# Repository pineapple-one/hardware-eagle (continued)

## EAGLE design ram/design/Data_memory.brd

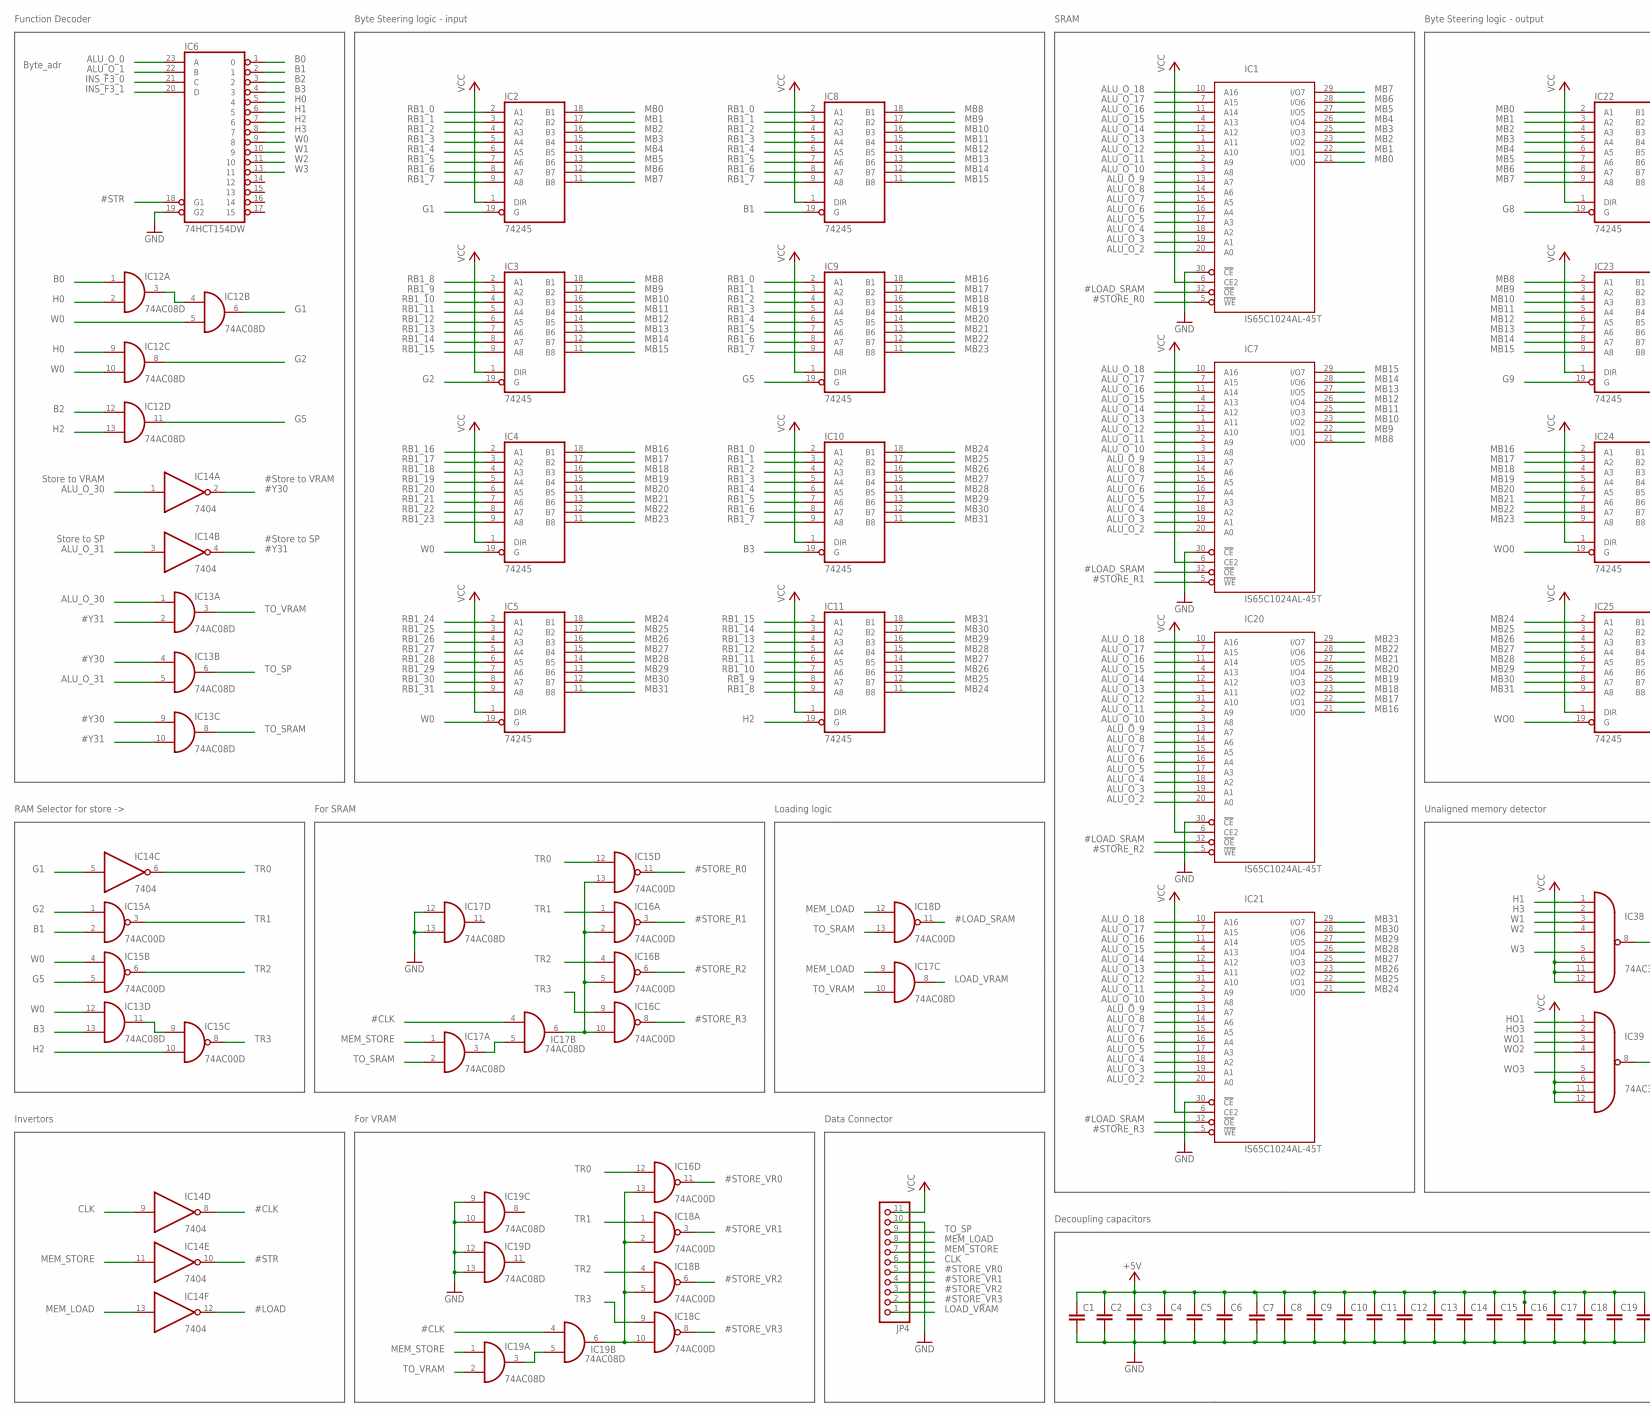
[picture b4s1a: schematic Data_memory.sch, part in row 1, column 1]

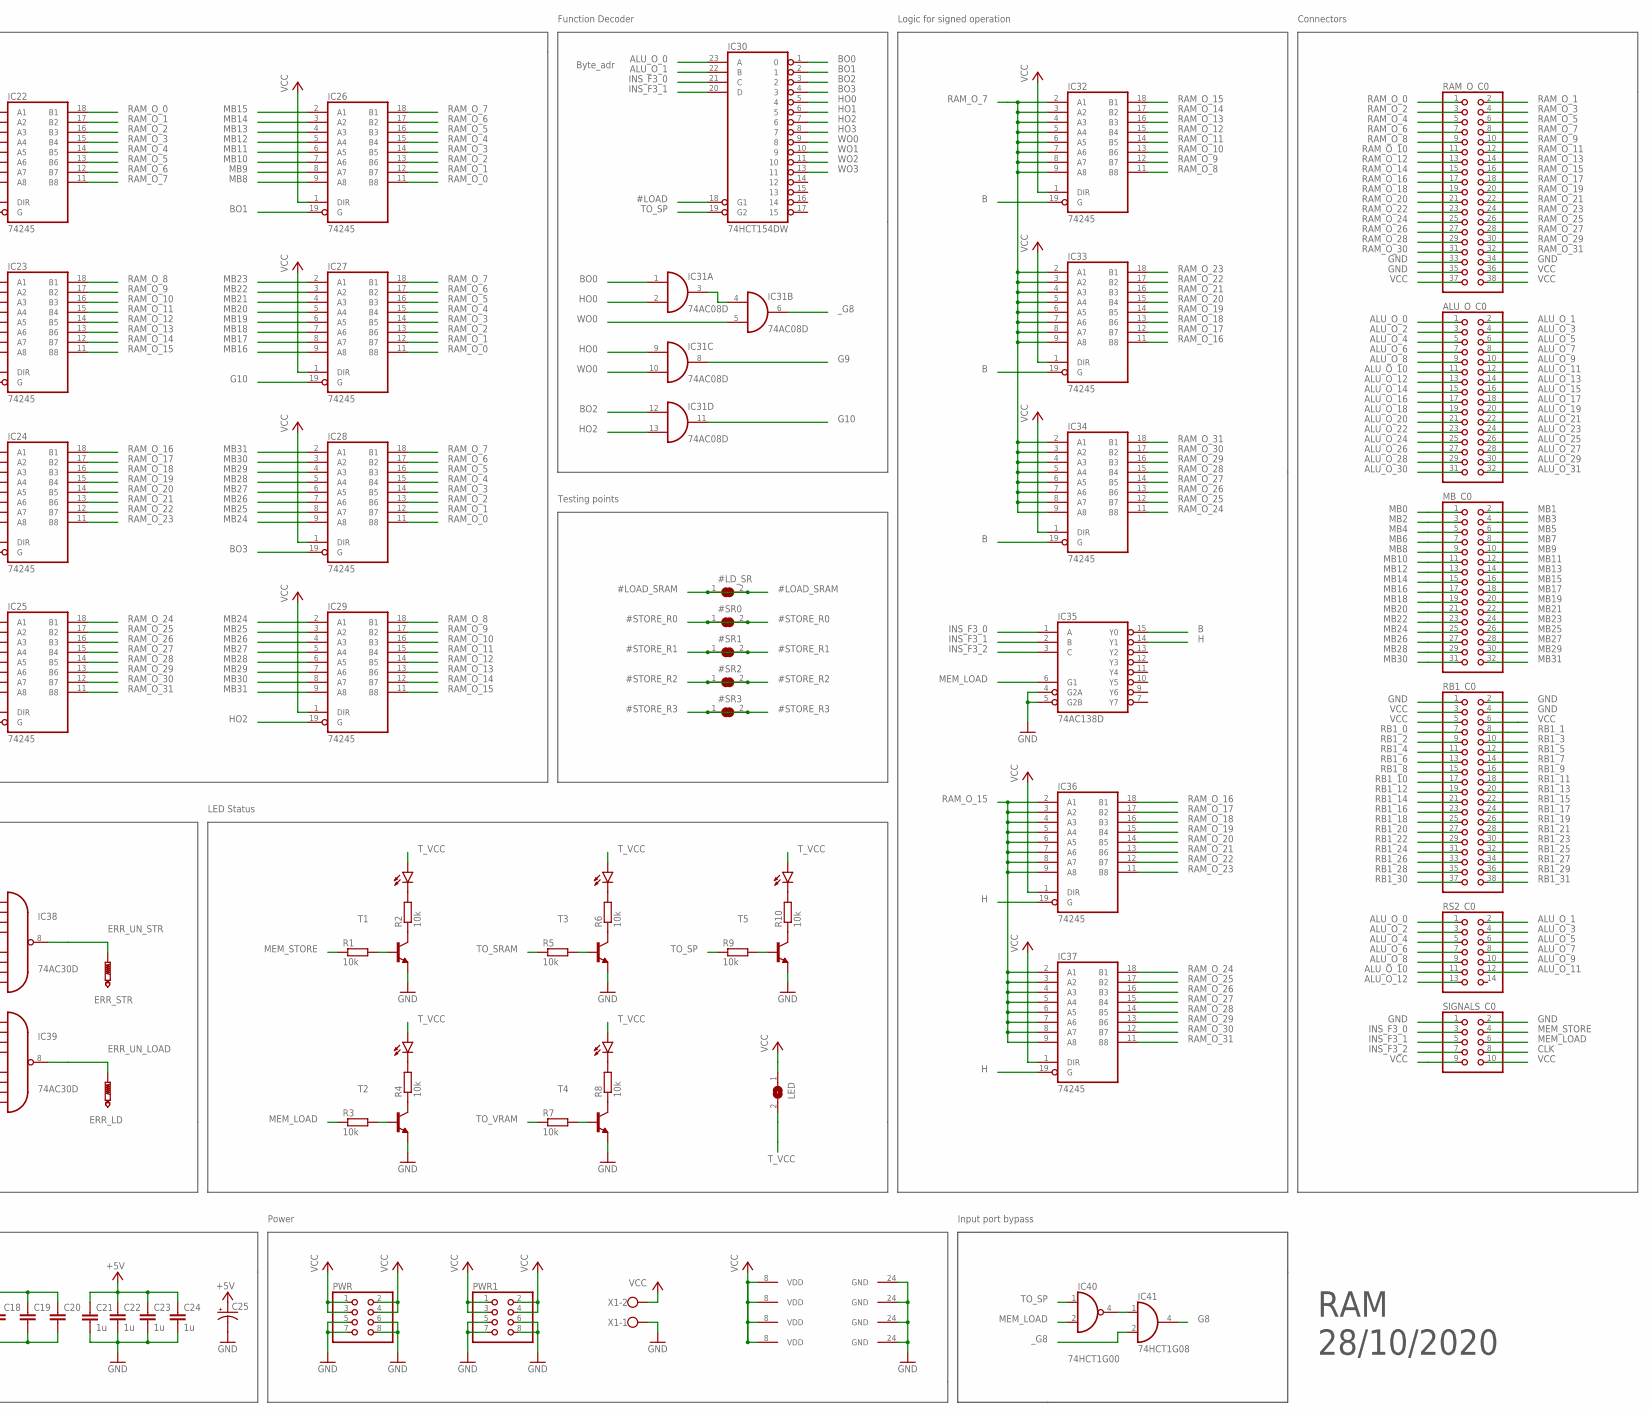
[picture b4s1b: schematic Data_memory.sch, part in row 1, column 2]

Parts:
#LD_SR: SJ
#SR0, #SR1, #SR2, #SR3: SJ
ALU_O_C0: PINHD-2X16; 2X16
C1, C2, C3, C4, C5, C6, C7, C8, C9, C10, C11, C12, C13, C14, C15, C16, C17, C18, C19, C20: C-EUC0805; C0805
C21, C22, C23, C24: 1u; C0805
C25: CAPACITOR-P153CLV-1010; 153CLV-1010
ERR_LD: PTR1B2,54; B2,54
ERR_STR: PTR1B2,54; B2,54
IC1, IC7, IC20, IC21: IS65C1024AL-45T; TSOP-I-32-8X20MM
IC2, IC3, IC4, IC5, IC8, IC9, IC10, IC11, IC22, IC23, IC24, IC25, IC26, IC27, IC28, IC29, IC32, IC33, IC34, IC36, IC37: 74245; TSSOP20
IC6, IC30: 74HCT154DW; SO24W
IC12, IC13, IC17, IC19, IC31: 74AC08D; SO14
IC14: 7404; TSSOP14
IC15, IC16, IC18: 74AC00D; SO14
IC35: 74AC138D; SO16
IC38, IC39: 74AC30D; SO14
IC40: 74HCT1G00; SOT23-5
IC41: 74HCT1G08; SOT23-5
JP4: PINHD-1X11; 1X11
LED: SJ
LED1, LED2, LED3, LED4, LED8: LEDSML0805; SML0805
MB_C0: PINHD-2X16; 2X16
PWR, PWR1: PINHD-2X4; 2X04
R1, R2, R3, R4, R5, R6, R7, R8, R9, R10: 10k; M0805
RAM_O_C0: PINHD-2X19; 2X19
RB1_C0: PINHD-2X19; 2X19
RS2_C0: PINHD-2X7; 2X07
SIGNALS_C0: PINHD-2X5; 2X05
T1, T2, T3, T4, T5: MMBT4401LT1-NPN-SOT23-BEC; SOT23-BEC
X1: W237-102

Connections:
#CLK: IC14.8 (O), IC17.4 (I0), IC19.4 (I0)
#LOAD: IC14.12 (O), IC30.18 (G1)
#LOAD_SRAM: #LD_SR.1, #LD_SR.2, IC1.32 (!OE), IC7.32 (!OE), IC18.11 (O), IC20.32 (!OE), IC21.32 (!OE)
#STORE_R0: #SR0.1, #SR0.2, IC1.5 (!WE), IC15.11 (O)
#STORE_R1: #SR1.1, #SR1.2, IC7.5 (!WE), IC16.3 (O)
#STORE_R2: #SR2.1, #SR2.2, IC16.6 (O), IC20.5 (!WE)
#STORE_R3: #SR3.1, #SR3.2, IC16.8 (O), IC21.5 (!WE)
#STORE_VR0: IC16.11 (O), JP4.5
#STORE_VR1: IC18.3 (O), JP4.4
#STORE_VR2: IC18.6 (O), JP4.3
#STORE_VR3: IC18.8 (O), JP4.2
#STR: IC6.18 (G1), IC14.10 (O)
#Y30: IC13.4 (I0), IC13.9 (I0), IC14.2 (O)
#Y31: IC13.2 (I1), IC13.10 (I1), IC14.4 (O)
ALU_O_0: ALU_O_C0.1, IC6.23 (A), IC30.23 (A), RS2_C0.1
ALU_O_1: ALU_O_C0.2, IC6.22 (B), IC30.22 (B), RS2_C0.2
ALU_O_2: ALU_O_C0.3, IC1.20 (A0), IC7.20 (A0), IC20.20 (A0), IC21.20 (A0), RS2_C0.3
ALU_O_3: ALU_O_C0.4, IC1.19 (A1), IC7.19 (A1), IC20.19 (A1), IC21.19 (A1), RS2_C0.4
ALU_O_4: ALU_O_C0.5, IC1.18 (A2), IC7.18 (A2), IC20.18 (A2), IC21.18 (A2), RS2_C0.5
ALU_O_5: ALU_O_C0.6, IC1.17 (A3), IC7.17 (A3), IC20.17 (A3), IC21.17 (A3), RS2_C0.6
ALU_O_6: ALU_O_C0.7, IC1.16 (A4), IC7.16 (A4), IC20.16 (A4), IC21.16 (A4), RS2_C0.7
ALU_O_7: ALU_O_C0.8, IC1.15 (A5), IC7.15 (A5), IC20.15 (A5), IC21.15 (A5), RS2_C0.8
ALU_O_8: ALU_O_C0.9, IC1.14 (A6), IC7.14 (A6), IC20.14 (A6), IC21.14 (A6), RS2_C0.9
ALU_O_9: ALU_O_C0.10, IC1.13 (A7), IC7.13 (A7), IC20.13 (A7), IC21.13 (A7), RS2_C0.10
ALU_O_10: ALU_O_C0.11, IC1.3 (A8), IC7.3 (A8), IC20.3 (A8), IC21.3 (A8), RS2_C0.11
ALU_O_11: ALU_O_C0.12, IC1.2 (A9), IC7.2 (A9), IC20.2 (A9), IC21.2 (A9), RS2_C0.12
ALU_O_12: ALU_O_C0.13, IC1.31 (A10), IC7.31 (A10), IC20.31 (A10), IC21.31 (A10), RS2_C0.13
ALU_O_13: ALU_O_C0.14, IC1.1 (A11), IC7.1 (A11), IC20.1 (A11), IC21.1 (A11)
ALU_O_14: ALU_O_C0.15, IC1.12 (A12), IC7.12 (A12), IC20.12 (A12), IC21.12 (A12)
ALU_O_15: ALU_O_C0.16, IC1.4 (A13), IC7.4 (A13), IC20.4 (A13), IC21.4 (A13)
ALU_O_16: ALU_O_C0.17, IC1.11 (A14), IC7.11 (A14), IC20.11 (A14), IC21.11 (A14)
ALU_O_17: ALU_O_C0.18, IC1.7 (A15), IC7.7 (A15), IC20.7 (A15), IC21.7 (A15)
ALU_O_18: ALU_O_C0.19, IC1.10 (A16), IC7.10 (A16), IC20.10 (A16), IC21.10 (A16)
ALU_O_19: ALU_O_C0.20
ALU_O_20: ALU_O_C0.21
ALU_O_21: ALU_O_C0.22
ALU_O_22: ALU_O_C0.23
ALU_O_23: ALU_O_C0.24
ALU_O_24: ALU_O_C0.25
ALU_O_25: ALU_O_C0.26
ALU_O_26: ALU_O_C0.27
ALU_O_27: ALU_O_C0.28
ALU_O_28: ALU_O_C0.29
ALU_O_29: ALU_O_C0.30
ALU_O_30: ALU_O_C0.31, IC13.1 (I0), IC14.1 (I)
ALU_O_31: ALU_O_C0.32, IC13.5 (I1), IC14.3 (I)
B: IC32.19 (G), IC33.19 (G), IC34.19 (G), IC35.15 (Y0)
B0: IC6.1 (0), IC12.1 (I0)
B1: IC6.2 (1), IC8.19 (G), IC15.2 (I1)
B2: IC6.3 (2), IC12.12 (I0)
B3: IC6.4 (3), IC10.19 (G), IC13.13 (I1)
BO0: IC30.1 (0), IC31.1 (I0)
BO1: IC26.19 (G), IC30.2 (1)
BO2: IC30.3 (2), IC31.12 (I0)
BO3: IC28.19 (G), IC30.4 (3)
CLK: IC14.9 (I), JP4.6, SIGNALS_C0.8
ERR_UN_LOAD: ERR_LD.TP, IC39.8 (O)
ERR_UN_STR: ERR_STR.TP, IC38.8 (O)
G1: IC2.19 (G), IC12.6 (O), IC14.5 (I)
G2: IC3.19 (G), IC12.8 (O), IC15.1 (I0)
G5: IC9.19 (G), IC12.11 (O), IC15.5 (I1)
G8: IC22.19 (G), IC41.4 (O)
G9: IC23.19 (G), IC31.8 (O)
G10: IC27.19 (G), IC31.11 (O)
GND: C1.2, C2.2, C3.2, C4.2, C5.2, C6.2, C7.2, C8.2, C9.2, C10.2, C11.2, C12.2, C13.2, C14.2, C15.2, C16.2, C17.2, C18.2, C19.2, C20.2, C21.2, C22.2, C23.2, C24.2, C25.-, IC1.24 (GND), IC1.30 (!CE), IC2.10 (GND), IC3.10 (GND), IC4.10 (GND), IC5.10 (GND), IC6.12 (GND), IC6.19 (G2), IC7.24 (GND), IC7.30 (!CE), IC8.10 (GND), IC9.10 (GND), IC10.10 (GND), IC11.10 (GND), IC12.7 (GND), IC13.7 (GND), IC14.7 (GND), IC15.7 (GND), IC16.7 (GND), IC17.7 (GND), IC17.12 (I0), IC17.13 (I1), IC18.7 (GND), IC19.7 (GND), IC19.9 (I0), IC19.10 (I1), IC19.12 (I0), IC19.13 (I1), IC20.24 (GND), IC20.30 (!CE), IC21.24 (GND), IC21.30 (!CE), IC22.10 (GND), IC23.10 (GND), IC24.10 (GND), IC25.10 (GND), IC26.10 (GND), IC27.10 (GND), IC28.10 (GND), IC29.10 (GND), IC30.12 (GND), IC31.7 (GND), IC32.10 (GND), IC33.10 (GND), IC34.10 (GND), IC35.4 (G2A), IC35.5 (G2B), IC35.8 (GND), IC36.10 (GND), IC37.10 (GND), IC38.7 (GND), IC39.7 (GND), IC40.3 (GND), IC41.3 (GND), JP4.10, PWR.5, PWR.6, PWR.7, PWR.8, PWR1.5, PWR1.6, PWR1.7, PWR1.8, RAM_O_C0.33, RAM_O_C0.34, RAM_O_C0.35, RB1_C0.1, RB1_C0.2, RB1_C0.4, SIGNALS_C0.1, SIGNALS_C0.2, T1.E, T2.E, T3.E, T4.E, T5.E, X1.1
H: IC35.14 (Y1), IC36.19 (G), IC37.19 (G)
H0: IC6.5 (4), IC12.2 (I1), IC12.9 (I0)
H1: IC6.6 (5), IC38.1 (I0)
H2: IC6.7 (6), IC11.19 (G), IC12.13 (I1), IC15.10 (I1)
H3: IC6.8 (7), IC38.2 (I1)
HO0: IC30.5 (4), IC31.2 (I1), IC31.9 (I0)
HO1: IC30.6 (5), IC39.1 (I0)
HO2: IC29.19 (G), IC30.7 (6), IC31.13 (I1)
HO3: IC30.8 (7), IC39.2 (I1)
INS_F3_0: IC6.21 (C), IC30.21 (C), IC35.1 (A), SIGNALS_C0.3
INS_F3_1: IC6.20 (D), IC30.20 (D), IC35.2 (B), SIGNALS_C0.5
INS_F3_2: IC35.3 (C), SIGNALS_C0.7
LOAD_VRAM: IC17.8 (O), JP4.1
MB0: IC1.21 (I/O0), IC2.18 (B1), IC22.2 (A1), MB_C0.1
MB1: IC1.22 (I/O1), IC2.17 (B2), IC22.3 (A2), MB_C0.2
MB2: IC1.23 (I/O2), IC2.16 (B3), IC22.4 (A3), MB_C0.3
MB3: IC1.25 (I/O3), IC2.15 (B4), IC22.5 (A4), MB_C0.4
MB4: IC1.26 (I/O4), IC2.14 (B5), IC22.6 (A5), MB_C0.5
MB5: IC1.27 (I/O5), IC2.13 (B6), IC22.7 (A6), MB_C0.6
MB6: IC1.28 (I/O6), IC2.12 (B7), IC22.8 (A7), MB_C0.7
MB7: IC1.29 (I/O7), IC2.11 (B8), IC22.9 (A8), MB_C0.8
MB8: IC3.18 (B1), IC7.21 (I/O0), IC8.18 (B1), IC23.2 (A1), IC26.9 (A8), MB_C0.9
MB9: IC3.17 (B2), IC7.22 (I/O1), IC8.17 (B2), IC23.3 (A2), IC26.8 (A7), MB_C0.10
MB10: IC3.16 (B3), IC7.23 (I/O2), IC8.16 (B3), IC23.4 (A3), IC26.7 (A6), MB_C0.11
MB11: IC3.15 (B4), IC7.25 (I/O3), IC8.15 (B4), IC23.5 (A4), IC26.6 (A5), MB_C0.12
MB12: IC3.14 (B5), IC7.26 (I/O4), IC8.14 (B5), IC23.6 (A5), IC26.5 (A4), MB_C0.13
MB13: IC3.13 (B6), IC7.27 (I/O5), IC8.13 (B6), IC23.7 (A6), IC26.4 (A3), MB_C0.14
MB14: IC3.12 (B7), IC7.28 (I/O6), IC8.12 (B7), IC23.8 (A7), IC26.3 (A2), MB_C0.15
MB15: IC3.11 (B8), IC7.29 (I/O7), IC8.11 (B8), IC23.9 (A8), IC26.2 (A1), MB_C0.16
MB16: IC4.18 (B1), IC9.18 (B1), IC20.21 (I/O0), IC24.2 (A1), IC27.9 (A8), MB_C0.17
MB17: IC4.17 (B2), IC9.17 (B2), IC20.22 (I/O1), IC24.3 (A2), IC27.8 (A7), MB_C0.18
MB18: IC4.16 (B3), IC9.16 (B3), IC20.23 (I/O2), IC24.4 (A3), IC27.7 (A6), MB_C0.19
MB19: IC4.15 (B4), IC9.15 (B4), IC20.25 (I/O3), IC24.5 (A4), IC27.6 (A5), MB_C0.20
MB20: IC4.14 (B5), IC9.14 (B5), IC20.26 (I/O4), IC24.6 (A5), IC27.5 (A4), MB_C0.21
MB21: IC4.13 (B6), IC9.13 (B6), IC20.27 (I/O5), IC24.7 (A6), IC27.4 (A3), MB_C0.22
MB22: IC4.12 (B7), IC9.12 (B7), IC20.28 (I/O6), IC24.8 (A7), IC27.3 (A2), MB_C0.23
MB23: IC4.11 (B8), IC9.11 (B8), IC20.29 (I/O7), IC24.9 (A8), IC27.2 (A1), MB_C0.24
MB24: IC5.18 (B1), IC10.18 (B1), IC11.11 (B8), IC21.21 (I/O0), IC25.2 (A1), IC28.9 (A8), IC29.2 (A1), MB_C0.25
MB25: IC5.17 (B2), IC10.17 (B2), IC11.12 (B7), IC21.22 (I/O1), IC25.3 (A2), IC28.8 (A7), IC29.3 (A2), MB_C0.26
MB26: IC5.16 (B3), IC10.16 (B3), IC11.13 (B6), IC21.23 (I/O2), IC25.4 (A3), IC28.7 (A6), IC29.4 (A3), MB_C0.27
MB27: IC5.15 (B4), IC10.15 (B4), IC11.14 (B5), IC21.25 (I/O3), IC25.5 (A4), IC28.6 (A5), IC29.5 (A4), MB_C0.28
MB28: IC5.14 (B5), IC10.14 (B5), IC11.15 (B4), IC21.26 (I/O4), IC25.6 (A5), IC28.5 (A4), IC29.6 (A5), MB_C0.29
MB29: IC5.13 (B6), IC10.13 (B6), IC11.16 (B3), IC21.27 (I/O5), IC25.7 (A6), IC28.4 (A3), IC29.7 (A6), MB_C0.30
MB30: IC5.12 (B7), IC10.12 (B7), IC11.17 (B2), IC21.28 (I/O6), IC25.8 (A7), IC28.3 (A2), IC29.8 (A7), MB_C0.31
MB31: IC5.11 (B8), IC10.11 (B8), IC11.18 (B1), IC21.29 (I/O7), IC25.9 (A8), IC28.2 (A1), IC29.9 (A8), MB_C0.32
MEM_LOAD: IC14.13 (I), IC17.9 (I0), IC18.12 (I0), IC35.6 (G1), IC40.2 (I1), JP4.8, R3.1, SIGNALS_C0.6
MEM_STORE: IC14.11 (I), IC17.1 (I0), IC19.1 (I0), JP4.7, R1.1, SIGNALS_C0.4
unnamed: IC12.3 (O), IC12.4 (I0)
unnamed: IC13.11 (O), IC15.9 (I0)
unnamed: IC17.3 (O), IC17.5 (I1)
unnamed: IC16.13 (I1), IC18.2 (I1), IC18.5 (I1), IC18.10 (I1), IC19.6 (O)
unnamed: IC19.3 (O), IC19.5 (I1)
unnamed: IC31.3 (O), IC31.4 (I0)
unnamed: IC15.13 (I1), IC16.2 (I1), IC16.5 (I1), IC16.10 (I1), IC17.6 (O)
unnamed: R1.2, T1.B
unnamed: R3.2, T2.B
unnamed: LED1.C, R2.2
unnamed: R2.1, T1.C
unnamed: LED8.C, R4.2
unnamed: R4.1, T2.C
unnamed: R5.2, T3.B
unnamed: LED2.C, R6.2
unnamed: R6.1, T3.C
unnamed: R7.2, T4.B
unnamed: LED3.C, R8.2
unnamed: R8.1, T4.C
unnamed: R9.2, T5.B
unnamed: LED4.C, R10.2
unnamed: R10.1, T5.C
unnamed: IC40.4 (O), IC41.1 (I0)
RAM_O_0: IC22.18 (B1), IC26.11 (B8), IC27.11 (B8), IC28.11 (B8), RAM_O_C0.1
RAM_O_1: IC22.17 (B2), IC26.12 (B7), IC27.12 (B7), IC28.12 (B7), RAM_O_C0.2
RAM_O_2: IC22.16 (B3), IC26.13 (B6), IC27.13 (B6), IC28.13 (B6), RAM_O_C0.3
RAM_O_3: IC22.15 (B4), IC26.14 (B5), IC27.14 (B5), IC28.14 (B5), RAM_O_C0.4
RAM_O_4: IC22.14 (B5), IC26.15 (B4), IC27.15 (B4), IC28.15 (B4), RAM_O_C0.5
RAM_O_5: IC22.13 (B6), IC26.16 (B3), IC27.16 (B3), IC28.16 (B3), RAM_O_C0.6
RAM_O_6: IC22.12 (B7), IC26.17 (B2), IC27.17 (B2), IC28.17 (B2), RAM_O_C0.7
RAM_O_7: IC22.11 (B8), IC26.18 (B1), IC27.18 (B1), IC28.18 (B1), IC32.2 (A1), IC32.3 (A2), IC32.4 (A3), IC32.5 (A4), IC32.6 (A5), IC32.7 (A6), IC32.8 (A7), IC32.9 (A8), IC33.2 (A1), IC33.3 (A2), IC33.4 (A3), IC33.5 (A4), IC33.6 (A5), IC33.7 (A6), IC33.8 (A7), IC33.9 (A8), IC34.2 (A1), IC34.3 (A2), IC34.4 (A3), IC34.5 (A4), IC34.6 (A5), IC34.7 (A6), IC34.8 (A7), IC34.9 (A8), RAM_O_C0.8
RAM_O_8: IC23.18 (B1), IC29.18 (B1), IC32.11 (B8), RAM_O_C0.9
RAM_O_9: IC23.17 (B2), IC29.17 (B2), IC32.12 (B7), RAM_O_C0.10
RAM_O_10: IC23.16 (B3), IC29.16 (B3), IC32.13 (B6), RAM_O_C0.11
RAM_O_11: IC23.15 (B4), IC29.15 (B4), IC32.14 (B5), RAM_O_C0.12
RAM_O_12: IC23.14 (B5), IC29.14 (B5), IC32.15 (B4), RAM_O_C0.13
RAM_O_13: IC23.13 (B6), IC29.13 (B6), IC32.16 (B3), RAM_O_C0.14
RAM_O_14: IC23.12 (B7), IC29.12 (B7), IC32.17 (B2), RAM_O_C0.15
RAM_O_15: IC23.11 (B8), IC29.11 (B8), IC32.18 (B1), IC36.2 (A1), IC36.3 (A2), IC36.4 (A3), IC36.5 (A4), IC36.6 (A5), IC36.7 (A6), IC36.8 (A7), IC36.9 (A8), IC37.2 (A1), IC37.3 (A2), IC37.4 (A3), IC37.5 (A4), IC37.6 (A5), IC37.7 (A6), IC37.8 (A7), IC37.9 (A8), RAM_O_C0.16
RAM_O_16: IC24.18 (B1), IC33.11 (B8), IC36.18 (B1), RAM_O_C0.17
RAM_O_17: IC24.17 (B2), IC33.12 (B7), IC36.17 (B2), RAM_O_C0.18
RAM_O_18: IC24.16 (B3), IC33.13 (B6), IC36.16 (B3), RAM_O_C0.19
RAM_O_19: IC24.15 (B4), IC33.14 (B5), IC36.15 (B4), RAM_O_C0.20
RAM_O_20: IC24.14 (B5), IC33.15 (B4), IC36.14 (B5), RAM_O_C0.21
RAM_O_21: IC24.13 (B6), IC33.16 (B3), IC36.13 (B6), RAM_O_C0.22
RAM_O_22: IC24.12 (B7), IC33.17 (B2), IC36.12 (B7), RAM_O_C0.23
RAM_O_23: IC24.11 (B8), IC33.18 (B1), IC36.11 (B8), RAM_O_C0.24
RAM_O_24: IC25.18 (B1), IC34.11 (B8), IC37.18 (B1), RAM_O_C0.25
RAM_O_25: IC25.17 (B2), IC34.12 (B7), IC37.17 (B2), RAM_O_C0.26
RAM_O_26: IC25.16 (B3), IC34.13 (B6), IC37.16 (B3), RAM_O_C0.27
RAM_O_27: IC25.15 (B4), IC34.14 (B5), IC37.15 (B4), RAM_O_C0.28
RAM_O_28: IC25.14 (B5), IC34.15 (B4), IC37.14 (B5), RAM_O_C0.29
RAM_O_29: IC25.13 (B6), IC34.16 (B3), IC37.13 (B6), RAM_O_C0.30
RAM_O_30: IC25.12 (B7), IC34.17 (B2), IC37.12 (B7), RAM_O_C0.31
RAM_O_31: IC25.11 (B8), IC34.18 (B1), IC37.11 (B8), RAM_O_C0.32
RB1_0: IC2.2 (A1), IC8.2 (A1), IC9.2 (A1), IC10.2 (A1), RB1_C0.7
RB1_1: IC2.3 (A2), IC8.3 (A2), IC9.3 (A2), IC10.3 (A2), RB1_C0.8
RB1_2: IC2.4 (A3), IC8.4 (A3), IC9.4 (A3), IC10.4 (A3), RB1_C0.9
RB1_3: IC2.5 (A4), IC8.5 (A4), IC9.5 (A4), IC10.5 (A4), RB1_C0.10
RB1_4: IC2.6 (A5), IC8.6 (A5), IC9.6 (A5), IC10.6 (A5), RB1_C0.11
RB1_5: IC2.7 (A6), IC8.7 (A6), IC9.7 (A6), IC10.7 (A6), RB1_C0.12
RB1_6: IC2.8 (A7), IC8.8 (A7), IC9.8 (A7), IC10.8 (A7), RB1_C0.13
RB1_7: IC2.9 (A8), IC8.9 (A8), IC9.9 (A8), IC10.9 (A8), RB1_C0.14
RB1_8: IC3.2 (A1), IC11.9 (A8), RB1_C0.15
RB1_9: IC3.3 (A2), IC11.8 (A7), RB1_C0.16
RB1_10: IC3.4 (A3), IC11.7 (A6), RB1_C0.17
RB1_11: IC3.5 (A4), IC11.6 (A5), RB1_C0.18
RB1_12: IC3.6 (A5), IC11.5 (A4), RB1_C0.19
RB1_13: IC3.7 (A6), IC11.4 (A3), RB1_C0.20
RB1_14: IC3.8 (A7), IC11.3 (A2), RB1_C0.21
RB1_15: IC3.9 (A8), IC11.2 (A1), RB1_C0.22
RB1_16: IC4.2 (A1), RB1_C0.23
RB1_17: IC4.3 (A2), RB1_C0.24
RB1_18: IC4.4 (A3), RB1_C0.25
RB1_19: IC4.5 (A4), RB1_C0.26
RB1_20: IC4.6 (A5), RB1_C0.27
RB1_21: IC4.7 (A6), RB1_C0.28
RB1_22: IC4.8 (A7), RB1_C0.29
RB1_23: IC4.9 (A8), RB1_C0.30
RB1_24: IC5.2 (A1), RB1_C0.31
RB1_25: IC5.3 (A2), RB1_C0.32
RB1_26: IC5.4 (A3), RB1_C0.33
RB1_27: IC5.5 (A4), RB1_C0.34
RB1_28: IC5.6 (A5), RB1_C0.35
RB1_29: IC5.7 (A6), RB1_C0.36
RB1_30: IC5.8 (A7), RB1_C0.37
RB1_31: IC5.9 (A8), RB1_C0.38
TO_SP: IC13.6 (O), IC30.19 (G2), IC40.1 (I0), JP4.9, R9.1
TO_SRAM: IC13.8 (O), IC17.2 (I1), IC18.13 (I1), R5.1
TO_VRAM: IC13.3 (O), IC17.10 (I1), IC19.2 (I1), R7.1
TR0: IC14.6 (O), IC15.12 (I0), IC16.12 (I0)
TR1: IC15.3 (O), IC16.1 (I0), IC18.1 (I0)
TR2: IC15.6 (O), IC16.4 (I0), IC18.4 (I0)
TR3: IC15.8 (O), IC16.9 (I0), IC18.9 (I0)
T_VCC: LED.2, LED1.A, LED2.A, LED3.A, LED4.A, LED8.A
VCC: C1.1, C2.1, C3.1, C4.1, C5.1, C6.1, C7.1, C8.1, C9.1, C10.1, C11.1, C12.1, C13.1, C14.1, C15.1, C16.1, C17.1, C18.1, C19.1, C20.1, C21.1, C22.1, C23.1, C24.1, C25.+, IC1.6 (CE2), IC1.8 (VDD), IC2.1 (DIR), IC2.20 (VCC), IC3.1 (DIR), IC3.20 (VCC), IC4.1 (DIR), IC4.20 (VCC), IC5.1 (DIR), IC5.20 (VCC), IC6.24 (VCC), IC7.6 (CE2), IC7.8 (VDD), IC8.1 (DIR), IC8.20 (VCC), IC9.1 (DIR), IC9.20 (VCC), IC10.1 (DIR), IC10.20 (VCC), IC11.1 (DIR), IC11.20 (VCC), IC12.14 (VCC), IC13.14 (VCC), IC14.14 (VCC), IC15.14 (VCC), IC16.14 (VCC), IC17.14 (VCC), IC18.14 (VCC), IC19.14 (VCC), IC20.6 (CE2), IC20.8 (VDD), IC21.6 (CE2), IC21.8 (VDD), IC22.1 (DIR), IC22.20 (VCC), IC23.1 (DIR), IC23.20 (VCC), IC24.1 (DIR), IC24.20 (VCC), IC25.1 (DIR), IC25.20 (VCC), IC26.1 (DIR), IC26.20 (VCC), IC27.1 (DIR), IC27.20 (VCC), IC28.1 (DIR), IC28.20 (VCC), IC29.1 (DIR), IC29.20 (VCC), IC30.24 (VCC), IC31.14 (VCC), IC32.1 (DIR), IC32.20 (VCC), IC33.1 (DIR), IC33.20 (VCC), IC34.1 (DIR), IC34.20 (VCC), IC35.16 (VCC), IC36.1 (DIR), IC36.20 (VCC), IC37.1 (DIR), IC37.20 (VCC), IC38.6 (I5), IC38.11 (I6), IC38.12 (I7), IC38.14 (VCC), IC39.6 (I5), IC39.11 (I6), IC39.12 (I7), IC39.14 (VCC), IC40.5 (VCC), IC41.5 (VCC), JP4.11, LED.1, PWR.1, PWR.2, PWR.3, PWR.4, PWR1.1, PWR1.2, PWR1.3, PWR1.4, RAM_O_C0.36, RAM_O_C0.37, RAM_O_C0.38, RB1_C0.3, RB1_C0.5, RB1_C0.6, SIGNALS_C0.9, SIGNALS_C0.10, X1.2
W0: IC4.19 (G), IC5.19 (G), IC6.9 (8), IC12.5 (I1), IC12.10 (I1), IC13.12 (I0), IC15.4 (I0)
W1: IC6.10 (9), IC38.3 (I2)
W2: IC6.11 (10), IC38.4 (I3)
W3: IC6.13 (11), IC38.5 (I4)
WO0: IC24.19 (G), IC25.19 (G), IC30.9 (8), IC31.5 (I1), IC31.10 (I1)
WO1: IC30.10 (9), IC39.3 (I2)
WO2: IC30.11 (10), IC39.4 (I3)
WO3: IC30.13 (11), IC39.5 (I4)
_G8: IC31.6 (O), IC41.2 (I1)

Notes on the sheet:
Byte_adr
Byte Steering logic - input
Function Decoder
Store to VRAM
#Store to VRAM
Store to SP
#Store to SP
RAM Selector for store ->
For SRAM
For VRAM
SRAM
Byte Steering logic - output
Unaligned memory detector
LED Status
Invertors
Loading logic
Data Connector
Decoupling capacitors
Logic for signed operation
Connectors
Power
Testing points
Input port bypass
RAM 28/10/2020

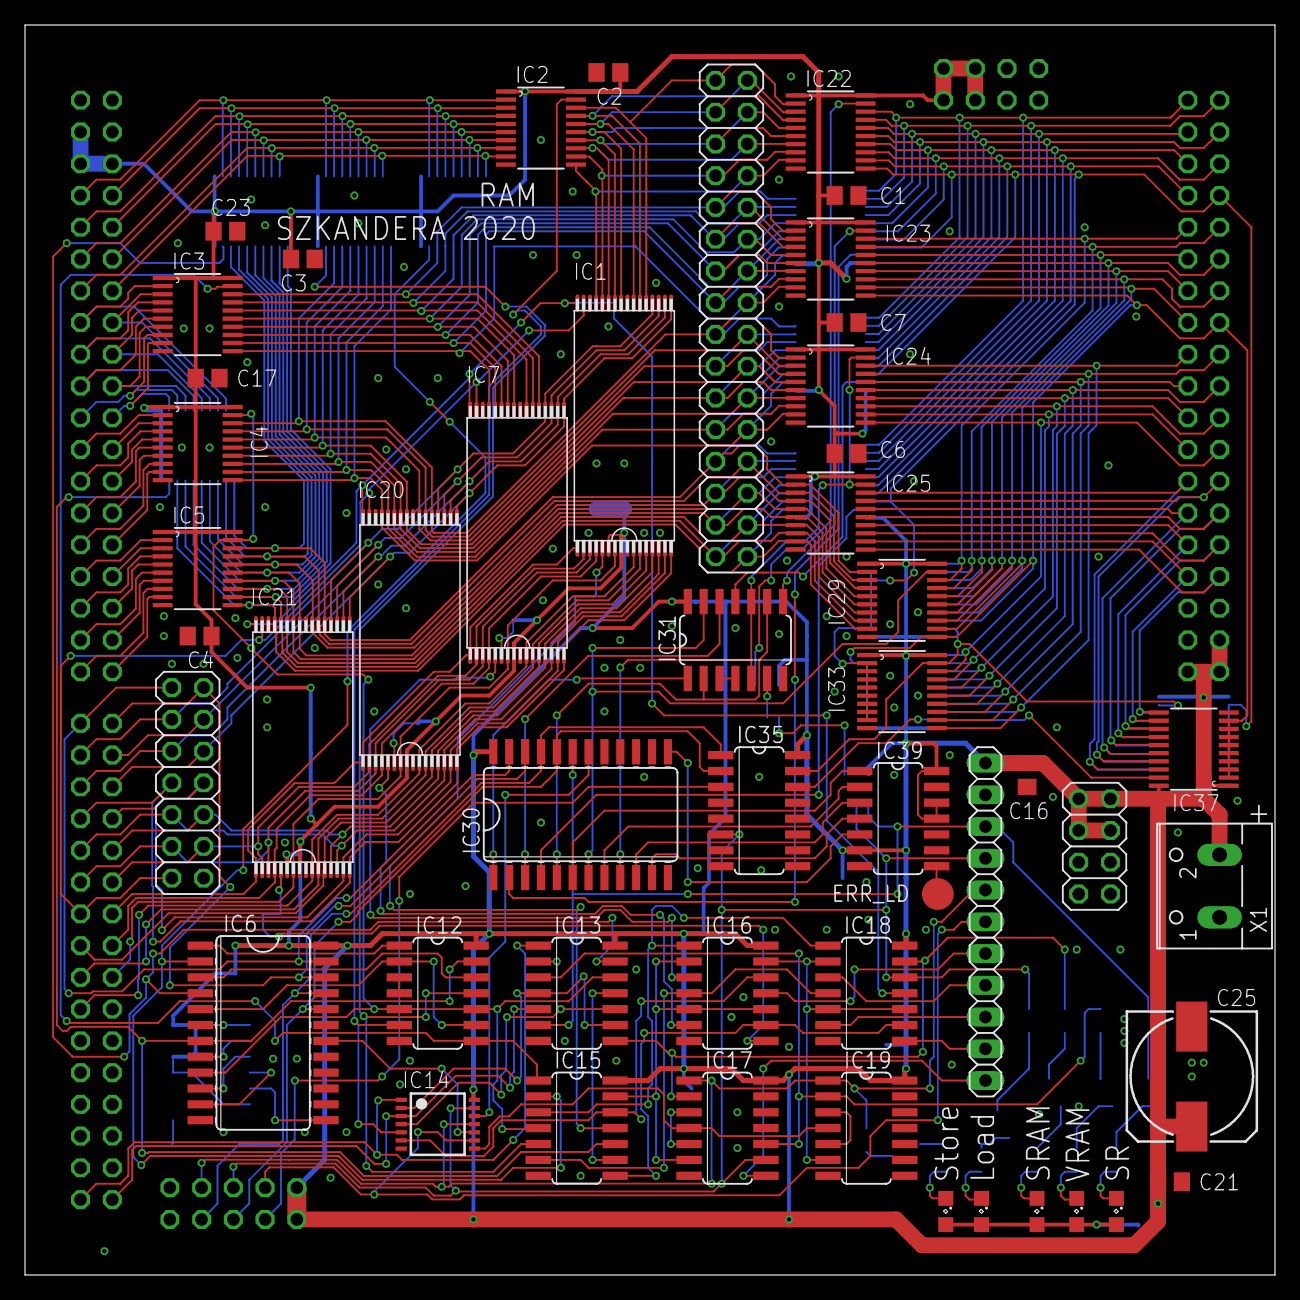
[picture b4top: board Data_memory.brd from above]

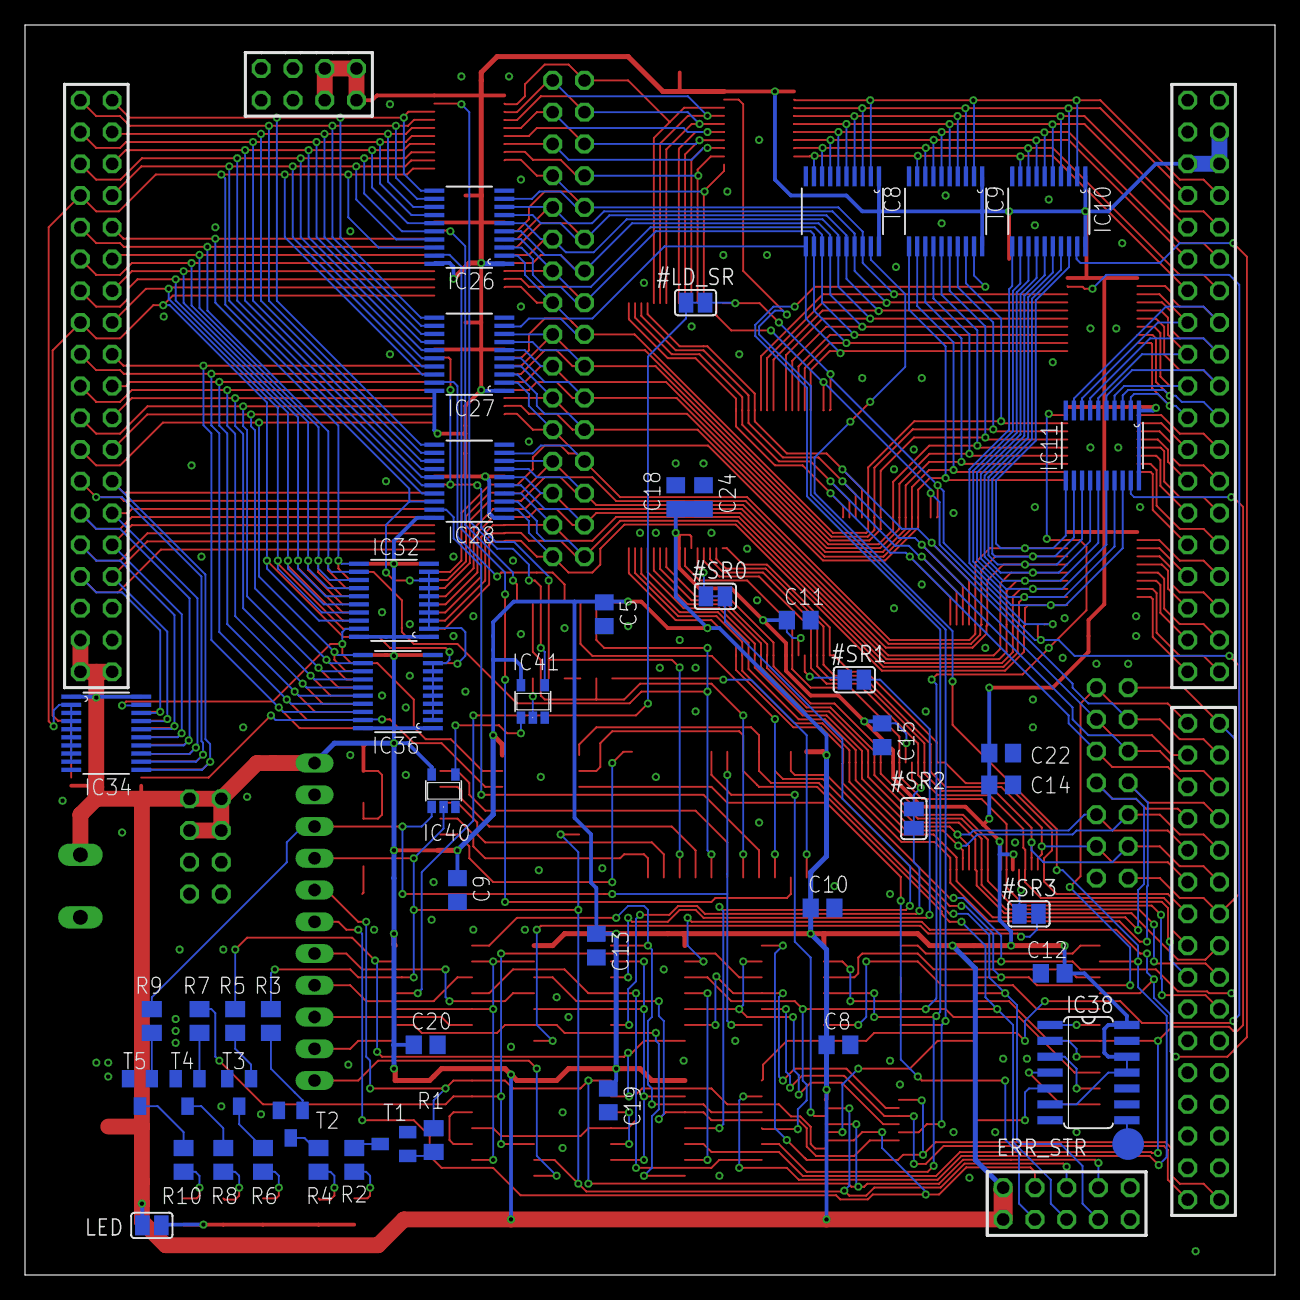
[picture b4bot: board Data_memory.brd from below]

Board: 2 copper layers, 100.0 x 100.0 mm, 104 parts (49 on the bottom side), 206 nets.
